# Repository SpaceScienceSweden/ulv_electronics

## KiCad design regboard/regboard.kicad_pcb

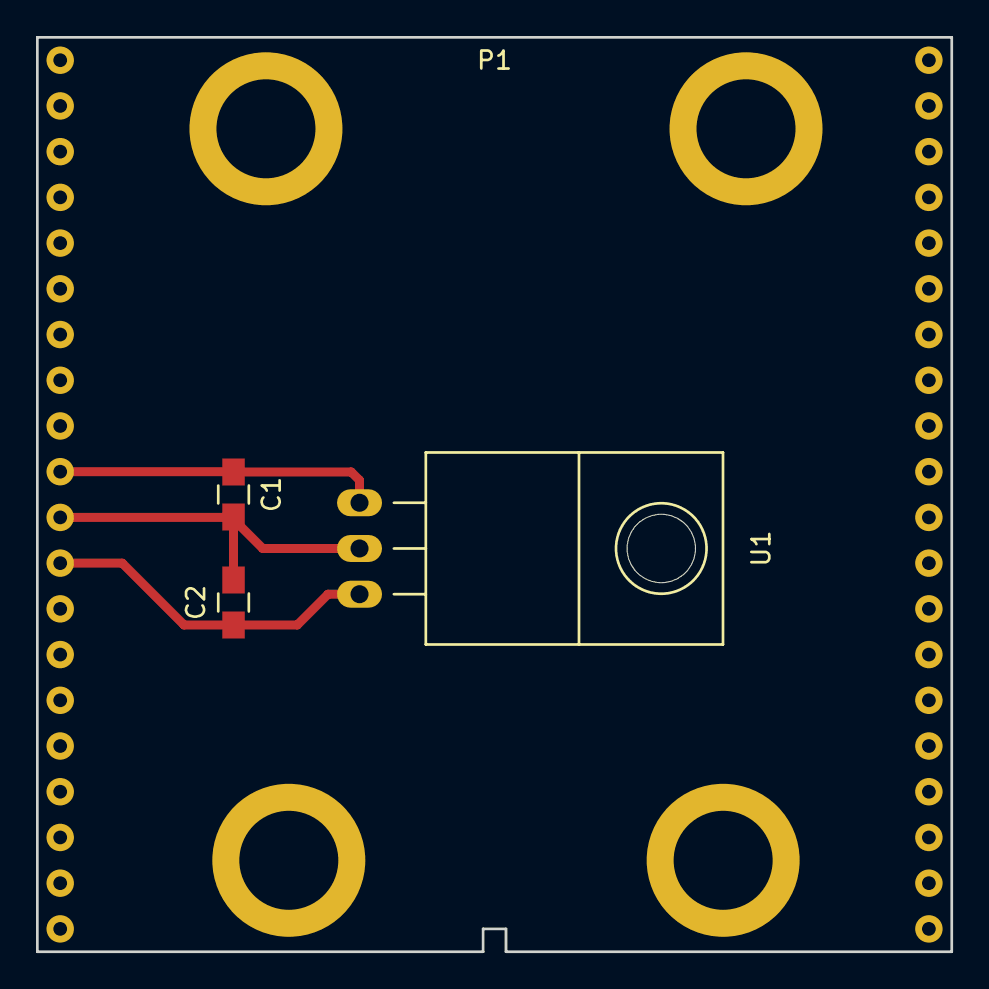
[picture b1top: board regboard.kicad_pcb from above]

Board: 2 copper layers, 50.8 x 50.8 mm, 4 parts (0 on the bottom side), 3 nets.

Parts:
C1: 10u; C_0805_HandSoldering
C2: 100n; C_0805_HandSoldering
P1: SCUBE40; scube40
U1: LM7812ACT; TO-220_Neutral123_Horizontal

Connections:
unnamed: C1.1, P1.10, U1.1
unnamed: C1.2, C2.2, P1.11, U1.2
unnamed: C2.1, P1.12, U1.3

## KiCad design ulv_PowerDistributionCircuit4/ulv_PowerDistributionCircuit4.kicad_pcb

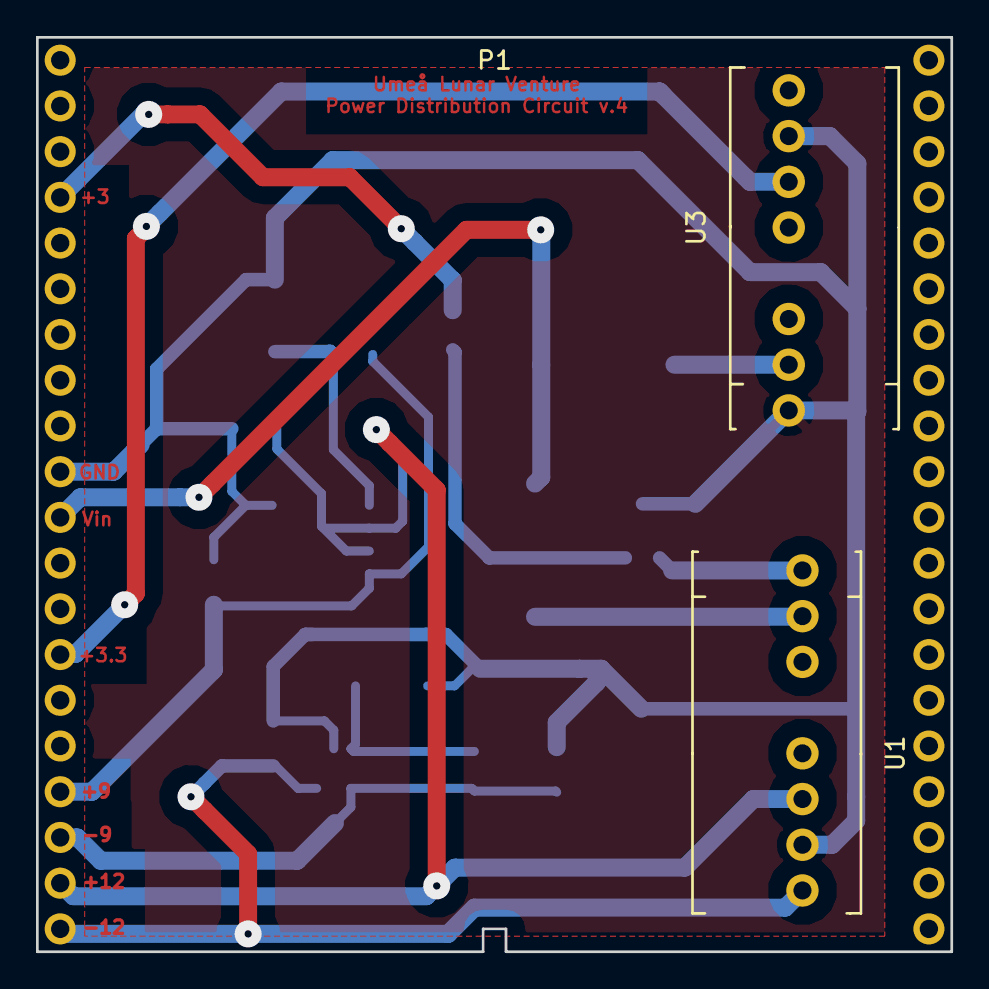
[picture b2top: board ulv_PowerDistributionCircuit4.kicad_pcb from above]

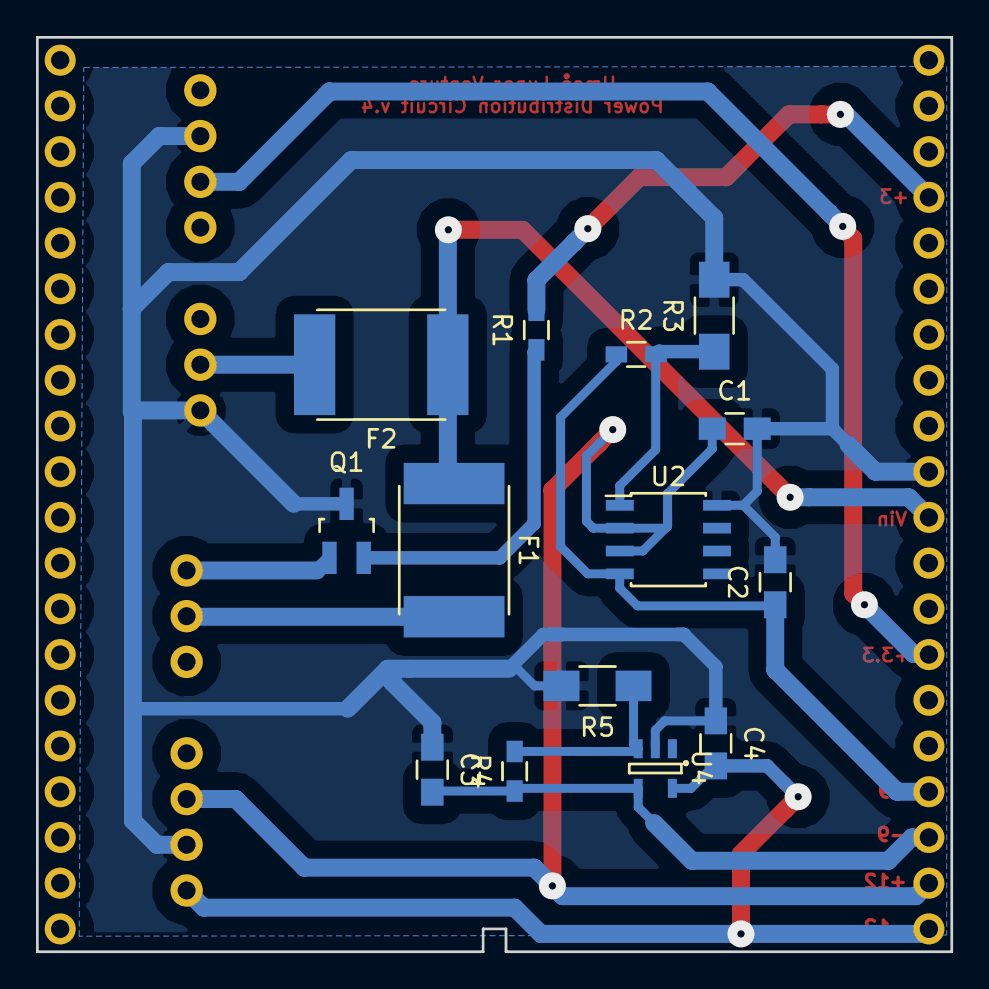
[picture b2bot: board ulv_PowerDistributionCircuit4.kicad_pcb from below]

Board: 2 copper layers, 50.8 x 50.8 mm, 17 parts (14 on the bottom side), 14 nets.

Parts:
C1: 0.1uF; C_0805_HandSoldering
C2, C3, C4: 10uF; C_0805_HandSoldering
F1, F2: F_Small; Fuse_SMD2920
P1: SCUBE40; scube40_no_holes
Q1: Q_NJFET_DGS; SOT-23_Handsoldering
R1: 10kO; R_0603_HandSoldering
R2, R4: 140kO; R_0603_HandSoldering
R3: 21.7kO; R_1206_HandSoldering
R5: 21.5kO; R_1206_HandSoldering
U1: RSO-2412D-Dual +/- 12V; RSO-2412D
U2: MAX1659 +9V; SOIC-8_3.9x4.9mm_Pitch1.27mm
U3: RSO-2412D-Single +3.3V; RSO-2412D
U4: MIC5270YM5-TR -9V; SOT-23-5

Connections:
unnamed: C1.1, P1.19, U1.6, U2.2, U2.3
unnamed: C1.2, C2.2, C3.1, C4.1, P1.10, Q1.3, R3.2, R5.2, U1.7, U2.8, U3.1, U3.7, U4.2
unnamed: C2.1, P1.17, R2.1, U2.4
unnamed: C3.2, P1.18, R4.1, U4.4
unnamed: C4.2, P1.20, U1.8, U4.5
unnamed: F1.1, F2.1, P1.11
unnamed: F1.2, U1.2
unnamed: F2.2, U3.2
unnamed: P1.4, R1.2
unnamed: P1.14, U3.6
unnamed: Q1.1, U1.1
unnamed: Q1.2, R1.1
unnamed: R2.2, R3.1, U2.1
unnamed: R4.2, R5.1, U4.3

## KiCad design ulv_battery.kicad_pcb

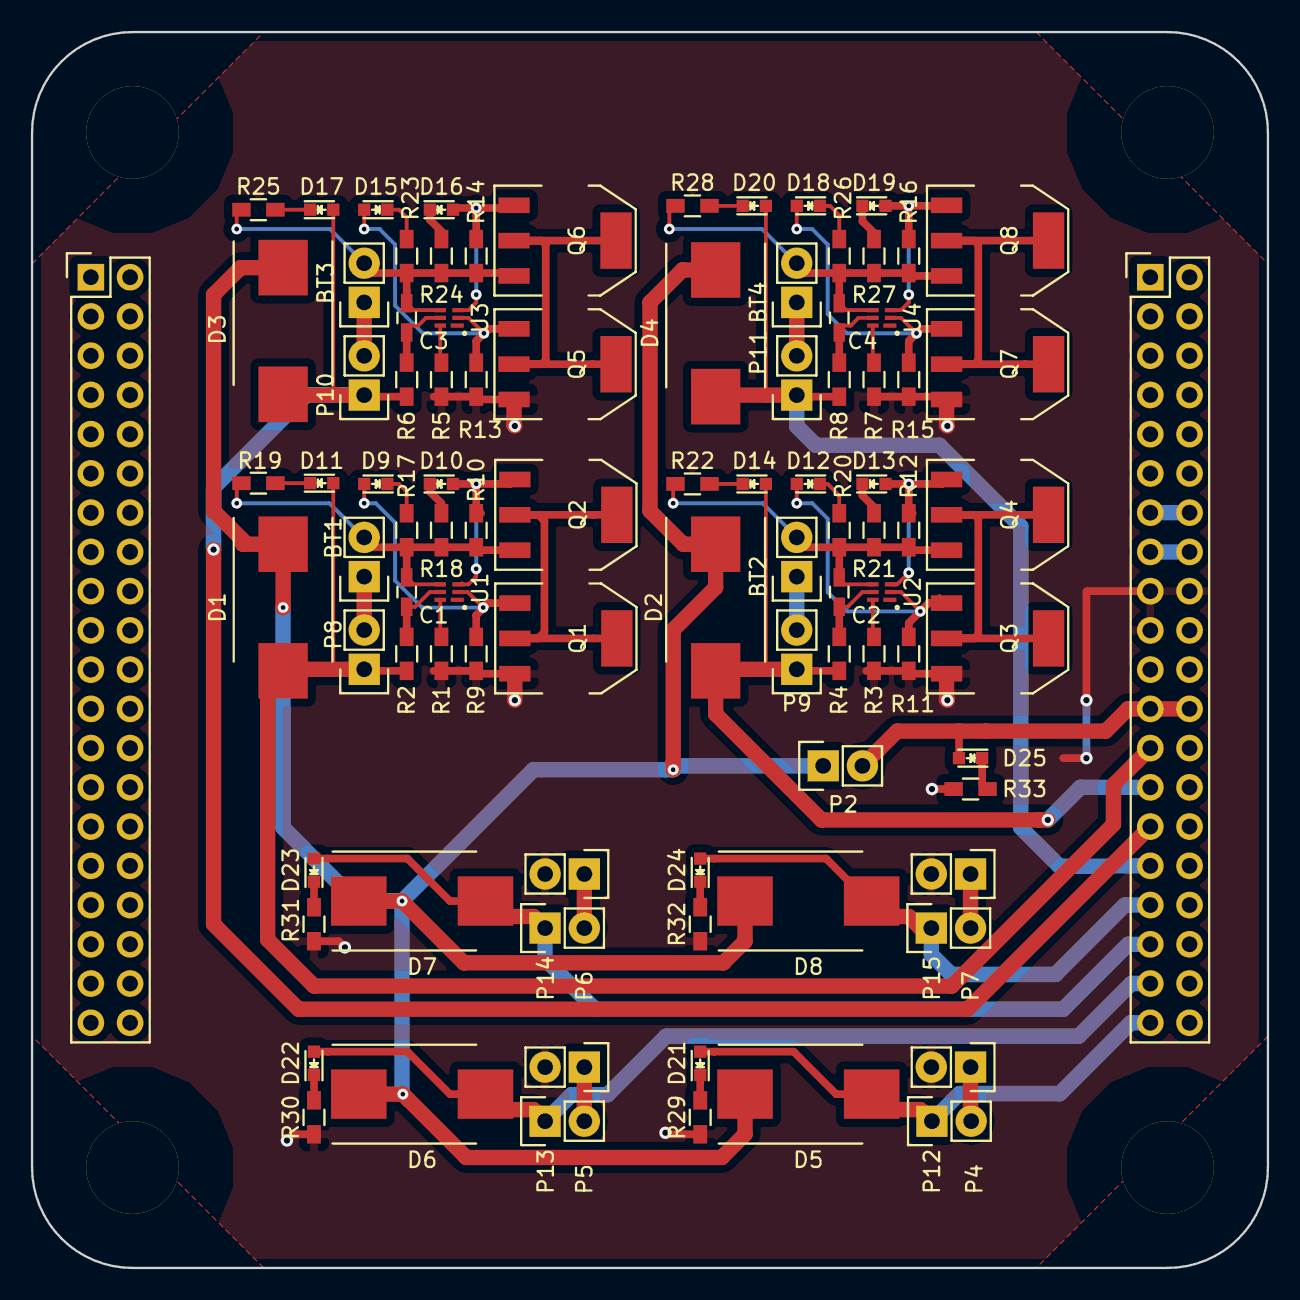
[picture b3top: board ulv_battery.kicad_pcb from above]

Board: 4 copper layers, 80.0 x 80.0 mm, 92 parts (0 on the bottom side), 62 nets.

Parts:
BT1, BT2, BT3, BT4: Battery; Pin_Header_Straight_1x02
C1, C2, C3, C4: 100n; C_0603_HandSoldering
D1, D2, D3, D4, D5, D6, D7, D8: Schottky; DO-214AB_Handsoldering
D9, D12, D15, D18, D25: GREEN; LED_0603
D10, D13, D16, D19: RED; LED_0603
D11, D14, D17, D20, D21, D22, D23, D24: ORANGE; LED_0603
P1: SCUBE80; scube80
P2, P8, P9, P10, P11, P12, P13, P14, P15: CONN_01X02; Pin_Header_Straight_1x02
P4, P5, P6, P7: PHOTOVOLTAIC; Pin_Header_Straight_1x02
Q1, Q2, Q3, Q4, Q5, Q6, Q7, Q8: Q_NMOS_GDSD; SOT-223
R1, R3, R5, R7, R17, R18, R19, R20, R21, R22, R23, R24, R25, R26, R27, R28, R29, R30, R31, R32, R33: 2k2; R_0603_HandSoldering
R2, R4, R6, R8: 330; R_0603_HandSoldering
R9, R10, R11, R12, R13, R14, R15, R16: 4M7; R_0603_HandSoldering
U1, U2, U3, U4: bq2970

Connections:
+3V3: P1.15A, P1.16A
+5V: P1.13A, P1.14A
/Battery 1/VBAT: D1.2, D11.2, P1.25A, P8.1, R2.1
/Battery 1/VSYS: D1.1, D2.1, D3.1, D4.1, D5.1, D6.1, D7.1, D8.1, P2.1
/Battery 2/VBAT: D2.2, D14.2, P1.27A, P9.1, R4.1
/Battery 3/VBAT: D3.2, D17.2, P1.29A, P10.1, R6.1
/Battery 4/VBAT: D4.2, D20.2, P1.31A, P11.1, R8.1
/Solar 1/VPV: D5.2, D21.2, P1.39A, P12.1
/Solar 2/VPV: D6.2, D22.2, P1.37A, P13.1
/Solar 3/VPV: D7.2, D23.2, P1.35A, P14.1
/Solar 4/VPV: D8.2, D24.2, P1.33A, P15.1
/VSYS: D25.2, P1.23A, P1.24A, P2.2
GND: P1.17A, P1.18A, P1.19A, P4.2, P5.2, P6.2, P7.2, Q1.3, Q3.3, Q5.3, Q7.3, R1.2, R3.2, R5.2, R7.2, R9.2, R11.2, R13.2, R15.2, R29.2, R30.2, R31.2, R32.2, R33.2
unnamed: BT1.1, P8.2
unnamed: BT1.2, C1.2, Q2.3, R10.2, R17.2, R18.2, R19.2, U1.4
unnamed: BT2.1, P9.2
unnamed: BT2.2, C2.2, Q4.3, R12.2, R20.2, R21.2, R22.2, U2.4
unnamed: BT3.1, P10.2
unnamed: BT3.2, C3.2, Q6.3, R14.2, R23.2, R24.2, R25.2, U3.4
unnamed: BT4.1, P11.2
unnamed: BT4.2, C4.2, Q8.3, R16.2, R26.2, R27.2, R28.2, U4.4
unnamed: C1.1, R2.2, U1.5
unnamed: C2.1, R4.2, U2.5
unnamed: C3.1, R6.2, U3.5
unnamed: C4.1, R8.2, U4.5
unnamed: D9.1, R17.1
unnamed: D9.2, Q1.1, R9.1, U1.2
unnamed: D10.1, R18.1
unnamed: D10.2, Q2.1, R10.1, U1.3
unnamed: D11.1, R19.1
unnamed: D12.1, R20.1
unnamed: D12.2, Q3.1, R11.1, U2.2
unnamed: D13.1, R21.1
unnamed: D13.2, Q4.1, R12.1, U2.3
unnamed: D14.1, R22.1
unnamed: D15.1, R23.1
unnamed: D15.2, Q5.1, R13.1, U3.2
unnamed: D16.1, R24.1
unnamed: D16.2, Q6.1, R14.1, U3.3
unnamed: D17.1, R25.1
unnamed: D18.1, R26.1
unnamed: D18.2, Q7.1, R15.1, U4.2
unnamed: D19.1, R27.1
unnamed: D19.2, Q8.1, R16.1, U4.3
unnamed: D20.1, R28.1
unnamed: D21.1, R29.1
unnamed: D22.1, R30.1
unnamed: D23.1, R31.1
unnamed: D24.1, R32.1
unnamed: D25.1, R33.1
unnamed: P4.1, P12.2
unnamed: P5.1, P13.2
unnamed: P6.1, P14.2
unnamed: P7.1, P15.2
unnamed: Q1.2, Q1.4, Q2.2, Q2.4
unnamed: Q3.2, Q3.4, Q4.2, Q4.4
unnamed: Q5.2, Q5.4, Q6.2, Q6.4
unnamed: Q7.2, Q7.4, Q8.2, Q8.4
unnamed: R1.1, U1.6
unnamed: R3.1, U2.6
unnamed: R5.1, U3.6
unnamed: R7.1, U4.6

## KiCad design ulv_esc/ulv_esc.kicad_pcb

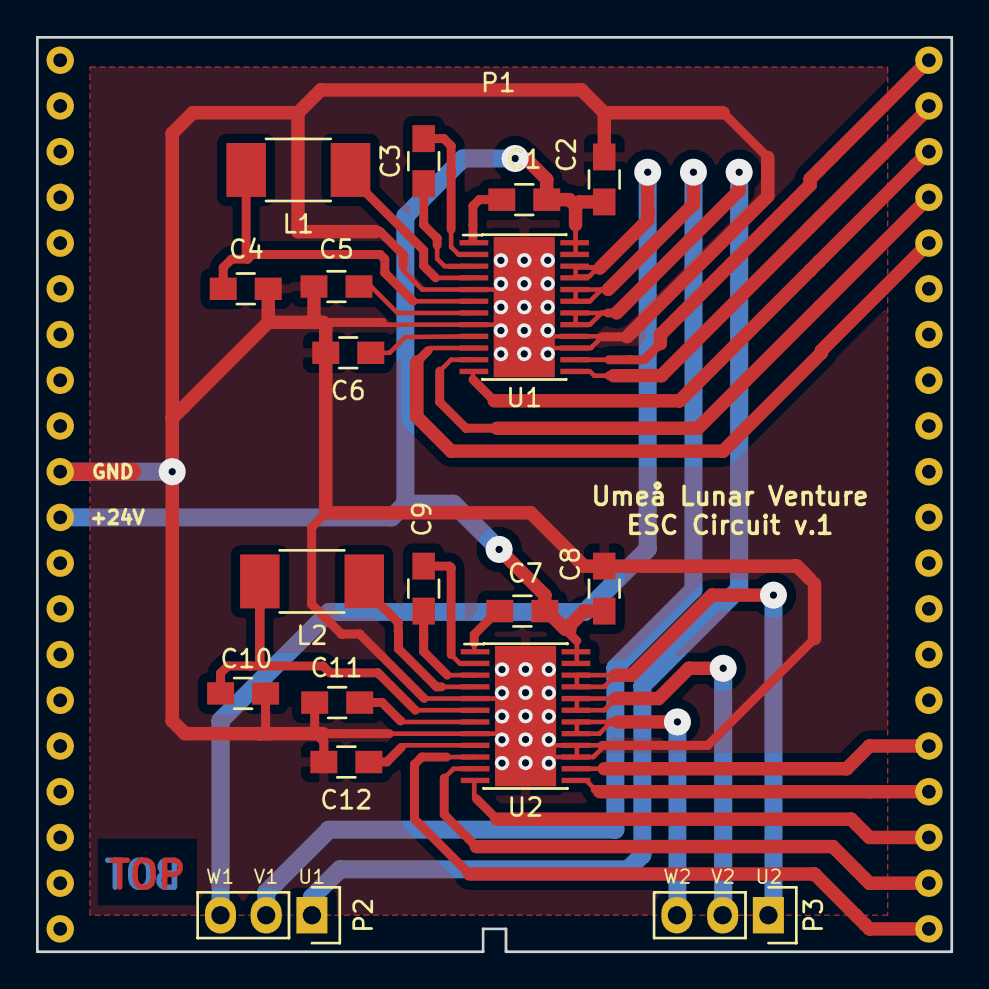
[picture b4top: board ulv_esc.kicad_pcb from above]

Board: 2 copper layers, 50.8 x 50.8 mm, 19 parts (0 on the bottom side), 32 nets.

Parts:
C1, C3, C7, C9: 0.1 uF; C_0805_HandSoldering
C2, C4, C8, C10: 10 uF; C_0805_HandSoldering
C5, C6, C11, C12: 1 uF; C_0805_HandSoldering
L1, L2: 47 uH; C_1812_HandSoldering
P1: SCUBE40; scube40_no_holes
P2, P3: CONN_01X03; Pin_Header_Straight_1x03
U1, U2: DRV10983; TSSOP-24_Pitch0.65mm_PowerPad

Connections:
GND: C2.2, C4.1, C5.2, C6.2, C8.2, C10.1, C11.2, C12.2, P1.10, U1.5, U1.8, U1.15, U1.16, U1.25, U2.5, U2.8, U2.15, U2.16, U2.25
unnamed: C1.1, C2.1, C7.1, C8.1, P1.11, U1.23, U1.24, U2.23, U2.24
unnamed: C1.2, U1.1
unnamed: C3.1, U1.3
unnamed: C3.2, U1.2
unnamed: C4.2, L1.2, U1.6
unnamed: C5.1, U1.7
unnamed: C6.1, U1.9
unnamed: C7.2, U2.1
unnamed: C9.1, U2.3
unnamed: C9.2, U2.2
unnamed: C10.2, L2.2, U2.6
unnamed: C11.1, U2.7
unnamed: C12.1, U2.9
unnamed: L1.1, U1.4
unnamed: L2.1, U2.4
unnamed: P1.21, U2.10
unnamed: P1.22, U2.11
unnamed: P1.23, U2.12
unnamed: P1.24, U2.13
unnamed: P1.25, U2.14
unnamed: P1.36, U1.10
unnamed: P1.37, U1.11
unnamed: P1.38, U1.12
unnamed: P1.39, U1.13
unnamed: P1.40, U1.14
unnamed: P2.1, U1.17, U1.18
unnamed: P2.2, U1.19, U1.20
unnamed: P2.3, U1.21, U1.22
unnamed: P3.1, U2.21, U2.22
unnamed: P3.2, U2.19, U2.20
unnamed: P3.3, U2.17, U2.18

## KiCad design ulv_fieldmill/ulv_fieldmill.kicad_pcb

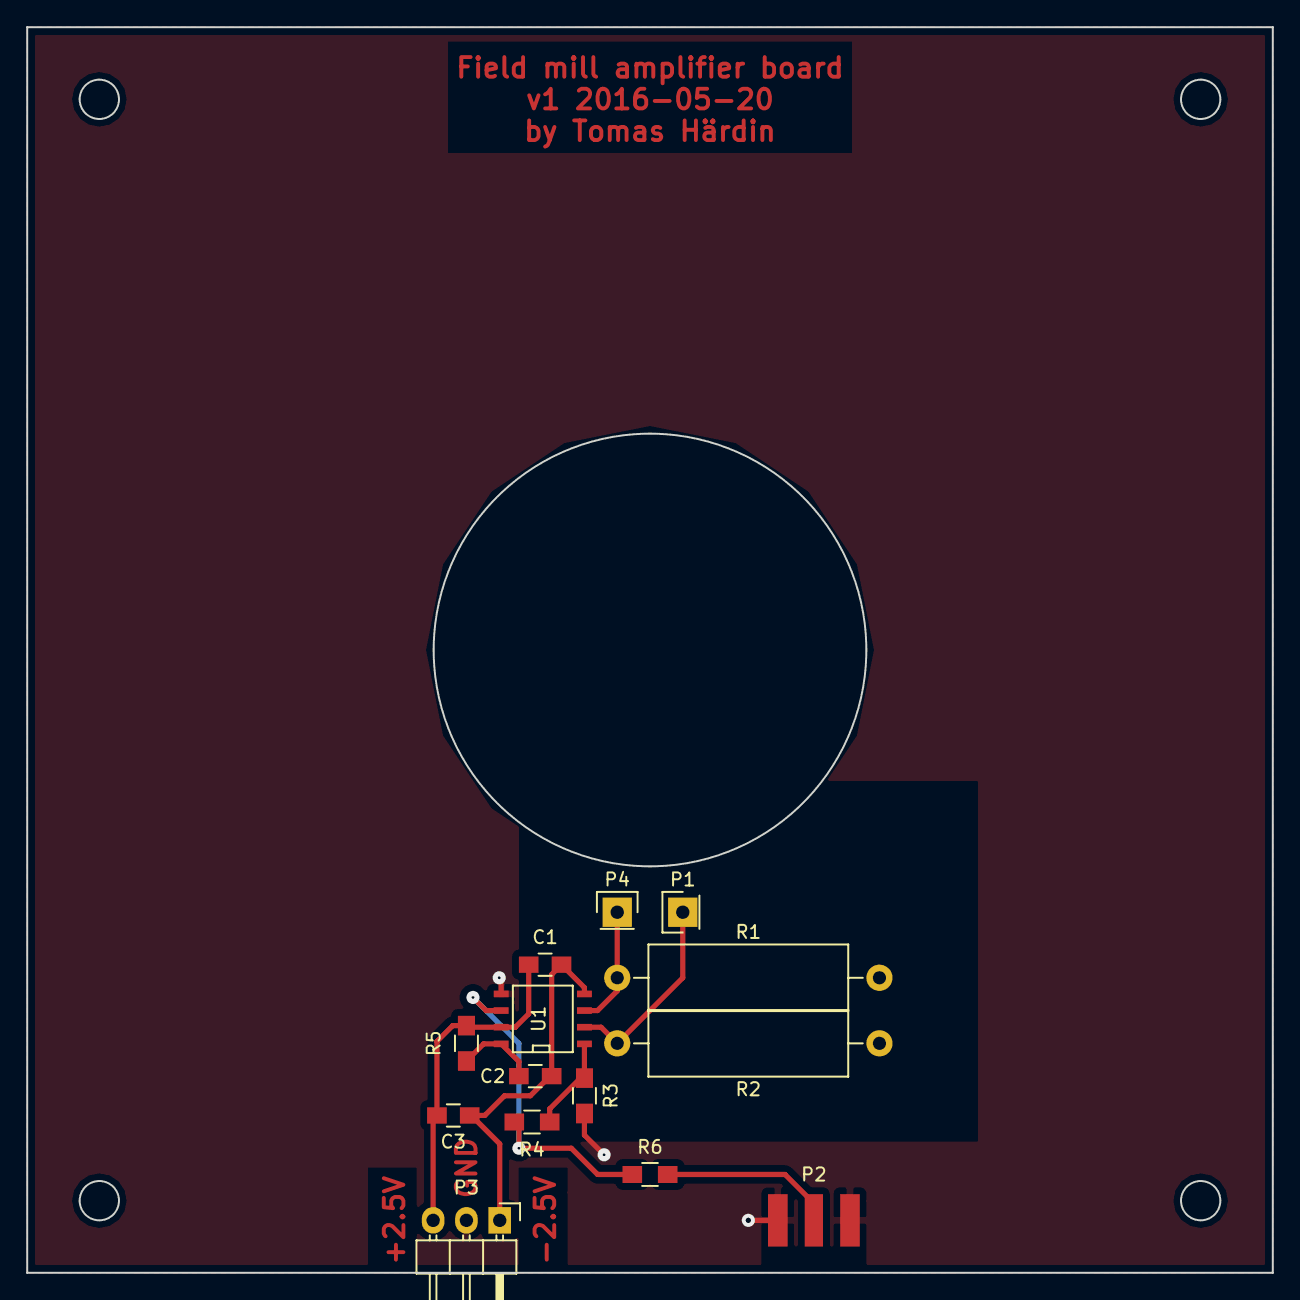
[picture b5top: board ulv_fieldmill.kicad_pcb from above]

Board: 2 copper layers, 95.0 x 95.0 mm, 14 parts (0 on the bottom side), 9 nets.

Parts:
C1, C2: 100n; C_0805_HandSoldering
C3: 1u; C_0805_HandSoldering
P1, P4: CONN_01X01; Pin_Header_Straight_1x01
P2: SMA; SMA-edge
P3: CONN_01X03; Pin_Header_Angled_1x03
R1, R2: 1M; Resistor_Horizontal_RM20mm
R3, R6: 1k; R_0805_HandSoldering
R4, R5: 100k; R_0805_HandSoldering
U1: MCP6N11; SOIC-8-N

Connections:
GND: P2.2, P3.2, R1.1, R2.1, R3.1, U1.5
unnamed: C2.1, R5.2, U1.8
unnamed: P1.1, R2.2, U1.2
unnamed: P2.1, R6.2
unnamed: P4.1, R1.2, U1.3
unnamed: R3.2, R4.1, U1.1
unnamed: R4.2, R6.1, U1.6
VDD: C1.1, C3.1, P3.3, R5.1, U1.7
VSS: C1.2, C2.2, C3.2, P3.1, U1.4

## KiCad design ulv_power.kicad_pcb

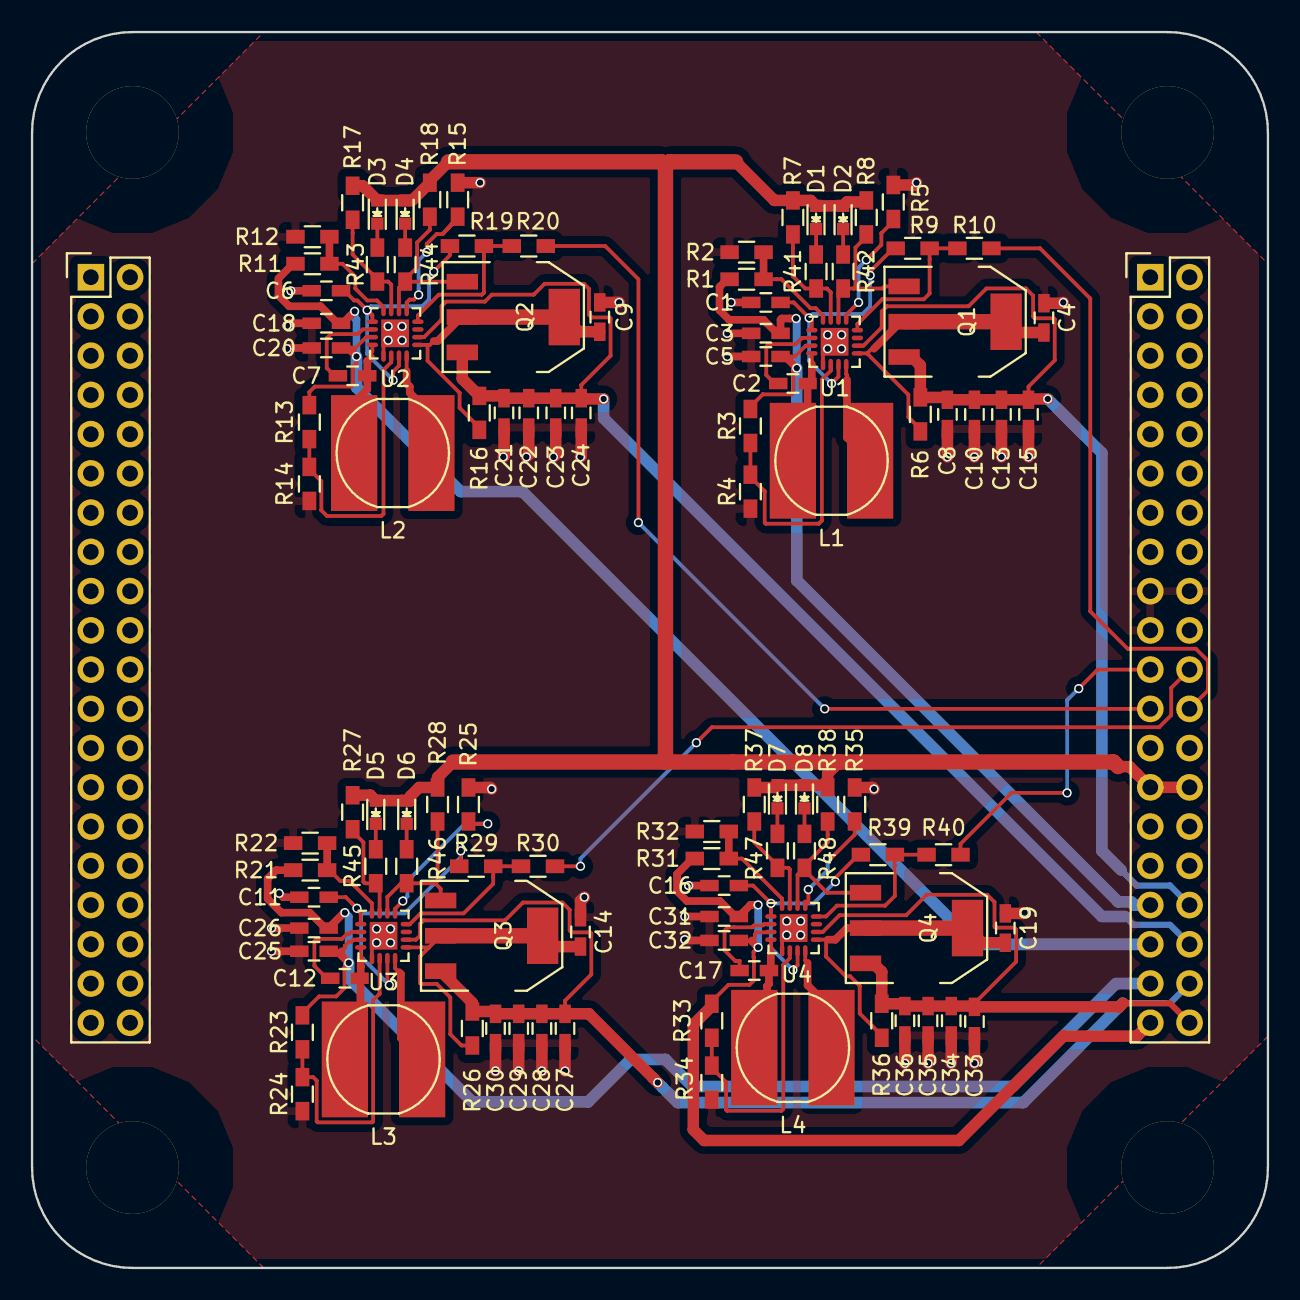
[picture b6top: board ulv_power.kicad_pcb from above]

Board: 4 copper layers, 80.0 x 80.0 mm, 105 parts (0 on the bottom side), 66 nets.

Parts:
C1, C6, C11, C16: 2.2uF; C_0603_HandSoldering
C2, C7, C12, C17: 22nF; C_0603_HandSoldering
C3, C4, C5, C8, C9, C10, C13, C14, C15, C18, C19, C20, C21, C22, C23, C24, C25, C26, C27, C28, C29, C30, C31, C32, C33, C34, C35, C36: 4.7uF; C_0603_HandSoldering
D1, D3, D5, D7: RED; LED_0603
D2, D4, D6, D8: GREEN; LED_0603
L1, L2, L3, L4: 12uH; SDE0805A
P1: SCUBE80; scube80
Q1, Q2, Q3, Q4: FDT434P; SOT-223
R1, R2, R7, R8, R11, R12, R17, R18, R21, R22, R27, R28, R31, R32, R37, R38: 47k; R_0603_HandSoldering
R3, R13, R23, R33: 10.0k; R_0603_HandSoldering
R4, R14, R24, R34: 1.67k; R_0603_HandSoldering
R5, R15, R25, R35: 3.01k; R_0603_HandSoldering
R6, R16, R26, R36: 470k; R_0603_HandSoldering
R9, R19, R29, R39: 8k2; R_0603_HandSoldering
R10, R20, R30, R40: 619; R_0603_HandSoldering
R41, R42, R43, R44, R45, R46, R47, R48: 2k2; R_0603_HandSoldering
U1, U2, U3, U4: LTC4121-4.2; QFN-16-1EP_3x3mm_Pitch0.5mm

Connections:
/chargerchannel1//CHRG: Q4.1, R38.1, R48.1, U4.14
/chargerchannel1//FAULT: R37.2, R47.1, U4.15
/chargerchannel1/NTC: P1.21A, R40.1
/chargerchannel1/PV_IN: C31.1, C32.1, P1.39A, R31.2, R33.2, U4.3
/chargerchannel1/RUN: R31.1, R32.1, U4.16
/chargerchannel1/VBAT: C33.1, C34.1, C35.1, C36.1, P1.40A, Q4.3, R36.1, U4.10
/chargerchannel1/VSYS: D1.2, D2.2, D3.2, D4.2, D5.2, D6.2, D7.2, D8.2, P1.27A, P1.28A, R7.1, R8.2, R17.1, R18.2, R27.1, R28.2, R37.1, R38.2
/chargerchannel2//CHRG: Q3.1, R28.1, R46.1, U3.14
/chargerchannel2//FAULT: R27.2, R45.1, U3.15
/chargerchannel2/NTC: P1.22A, R30.1
/chargerchannel2/PV_IN: C25.1, C26.1, P1.37A, R21.2, R23.2, U3.3
/chargerchannel2/RUN: R21.1, R22.1, U3.16
/chargerchannel2/VBAT: C27.1, C28.1, C29.1, C30.1, P1.38A, Q3.3, R26.1, U3.10
/chargerchannel3//CHRG: Q2.1, R18.1, R44.1, U2.14
/chargerchannel3//FAULT: R17.2, R43.1, U2.15
/chargerchannel3/NTC: P1.23A, R20.1
/chargerchannel3/PV_IN: C18.1, C20.1, P1.35A, R11.2, R13.2, U2.3
/chargerchannel3/RUN: R11.1, R12.1, U2.16
/chargerchannel3/VBAT: C21.1, C22.1, C23.1, C24.1, P1.36A, Q2.3, R16.1, U2.10
/chargerchannel4//CHRG: Q1.1, R8.1, R42.1, U1.14
/chargerchannel4//FAULT: R7.2, R41.1, U1.15
/chargerchannel4/NTC: P1.24A, R10.1
/chargerchannel4/PV_IN: C3.1, C5.1, P1.33A, R1.2, R3.2, U1.3
/chargerchannel4/RUN: R1.1, R2.1, U1.16
/chargerchannel4/VBAT: C8.1, C10.1, C13.1, C15.1, P1.34A, Q1.3, R6.1, U1.10
GND: C1.1, C3.2, C4.2, C5.2, C6.1, C8.2, C9.2, C10.2, C11.1, C13.2, C14.2, C15.2, C16.1, C18.2, C19.2, C20.2, C21.2, C22.2, C23.2, C24.2, C25.2, C26.2, C27.2, C28.2, C29.2, C30.2, C31.2, C32.2, C33.2, C34.2, C35.2, C36.2, P1.17A, P1.18A, P1.19A, R2.2, R4.2, R5.1, R12.2, R14.2, R15.1, R22.2, R24.2, R25.1, R32.2, R34.2, R35.1, U1.5, U1.17, U2.5, U2.17, U3.5, U3.17, U4.5, U4.17
unnamed: C1.2, R9.2, U1.1, U1.7
unnamed: C2.1, L1.1, U1.4
unnamed: C2.2, U1.2
unnamed: C4.1, Q1.2, Q1.4, R6.2, U1.9
unnamed: C6.2, R19.2, U2.1, U2.7
unnamed: C7.1, L2.1, U2.4
unnamed: C7.2, U2.2
unnamed: C9.1, Q2.2, Q2.4, R16.2, U2.9
unnamed: C11.2, R29.2, U3.1, U3.7
unnamed: C12.1, L3.1, U3.4
unnamed: C12.2, U3.2
unnamed: C14.1, Q3.2, Q3.4, R26.2, U3.9
unnamed: C16.2, R39.2, U4.1, U4.7
unnamed: C17.1, L4.1, U4.4
unnamed: C17.2, U4.2
unnamed: C19.1, Q4.2, Q4.4, R36.2, U4.9
unnamed: D1.1, R41.2
unnamed: D2.1, R42.2
unnamed: D3.1, R43.2
unnamed: D4.1, R44.2
unnamed: D5.1, R45.2
unnamed: D6.1, R46.2
unnamed: D7.1, R47.2
unnamed: D8.1, R48.2
unnamed: L1.2, U1.8
unnamed: L2.2, U2.8
unnamed: L3.2, U3.8
unnamed: L4.2, U4.8
unnamed: R3.1, R4.1, U1.6
unnamed: R5.2, U1.13
unnamed: R9.1, R10.2, U1.12
unnamed: R13.1, R14.1, U2.6
unnamed: R15.2, U2.13
unnamed: R19.1, R20.2, U2.12
unnamed: R23.1, R24.1, U3.6
unnamed: R25.2, U3.13
unnamed: R29.1, R30.2, U3.12
unnamed: R33.1, R34.1, U4.6
unnamed: R35.2, U4.13
unnamed: R39.1, R40.2, U4.12

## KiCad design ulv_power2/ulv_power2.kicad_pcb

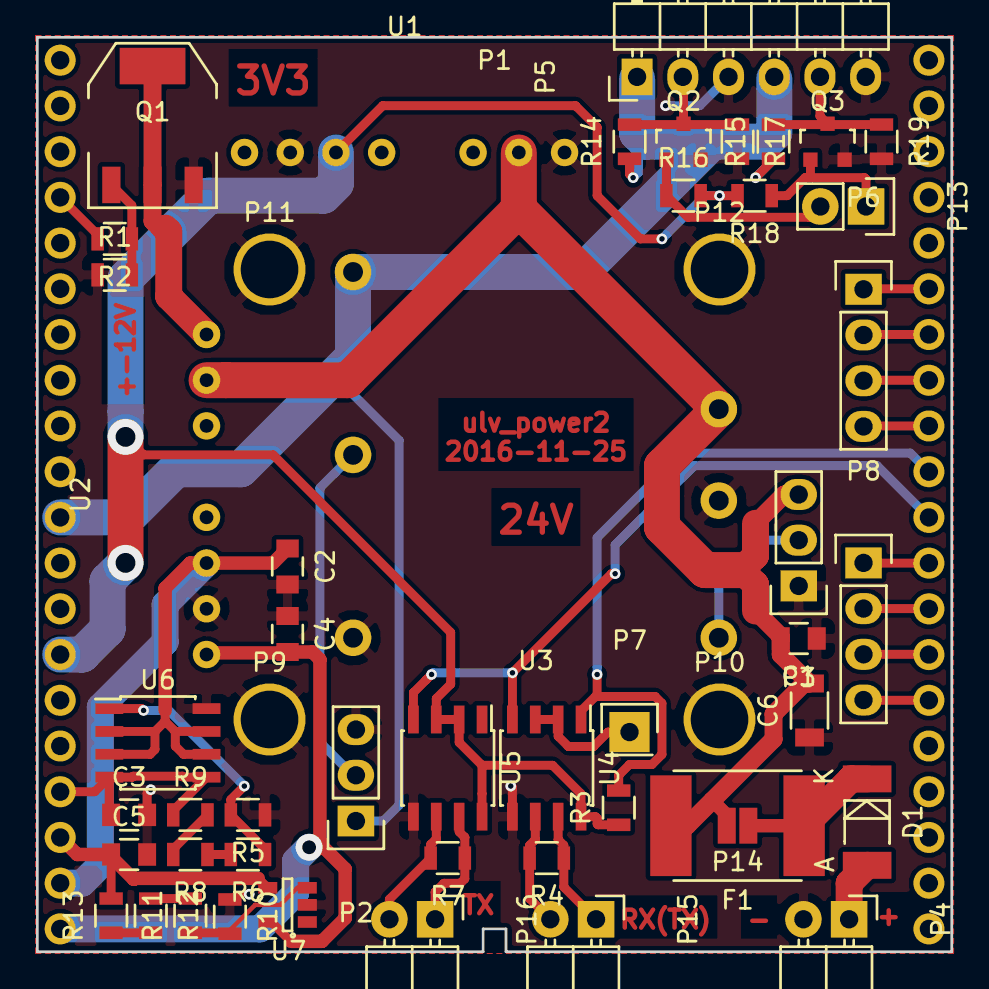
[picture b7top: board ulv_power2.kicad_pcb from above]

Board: 2 copper layers, 50.8 x 50.8 mm, 53 parts (0 on the bottom side), 40 nets.

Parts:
C1, C3, C5: 10u; C_0805
C2, C4: 100n; C_0805
C6: 100u; C_1206
D1: SMS240; MELF_Standard
F1: PTC; Fuse_SMD2920
P1: SCUBE40; scube40_no_holes
P2: TRIM; Pin_Header_Straight_1x03
P3: ON/OFF; Pin_Header_Straight_1x03
P4: PWR; Pin_Header_Angled_1x02
P5: MOTOR_OUT; Pin_Header_Angled_1x06
P6: DE2; Pin_Header_Straight_1x04
P7: DE; Pin_Header_Straight_1x01
P8: DE1; Pin_Header_Straight_1x04
P9, P10, P11, P12: M3; M3_PTH
P13: PWM; Pin_Header_Straight_1x02
P14: FUSE_BYPASS; solder_bridge
P15: IN; Pin_Header_Angled_1x02
P16: OUT; Pin_Header_Angled_1x02
Q1: IRLL024NPBF; SOT-223
Q2, Q3: PMBF170; SOT-23
R1: 1M; R_0805
R2, R3, R5, R10: 10k; R_0805
R4, R7: 120; R_0805
R6, R11: 56k; R_0805
R8, R12: 8k2; R_0805
R9: 180; R_0805
R13: 820; R_0805
R14, R15, R16, R17, R18, R19: 100k; R_0805
U1: RS-243.3S; RSO-2412D_v2
U2: RSO-2412D-Dual; RSO-2412D_v2
U3: THN_30-2415
U4, U5: MAX485; SOIC-8_3.9x4.9mm_Pitch1.27mm
U6: MAX1659; SOIC-8_3.9x4.9mm_Pitch1.27mm
U7: MIC5270YM5-TR; SOT-23-5

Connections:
+3V3: P1.14, R3.1, R16.2, R18.2, U1.6, U4.8, U5.2, U5.3, U5.8
+9V: C3.1, P1.17, R9.1, U6.4, U6.5
+12V: C2.1, P1.19, U2.6, U6.2, U6.3, U6.6, U6.7
+24V: P1.11, P2.1, P5.1, P5.4, R14.1, R15.1, U3.3
-9VA: C5.1, P1.18, R13.2, U7.4
-12VA: C4.2, P1.20, U2.8, U7.5
/A: P15.2, R4.2, U4.6
/B: P15.1, R4.1, U4.7
/EN_APWR: P1.4, R2.2
/RX: P1.31, R3.2, U4.1
/TX: P1.30, U4.4, U5.4
/Y: P16.2, R7.2, U5.6
/Z: P16.1, R7.1, U5.7
GND: C1.1, C2.2, C3.2, C4.1, C5.2, C6.1, P1.10, P2.3, P3.1, P4.2, P5.3, P5.6, P9.1, P10.1, P11.1, P12.1, Q1.3, Q2.2, Q3.2, R1.1, R5.1, R10.1, R17.2, R19.2, U1.1, U1.7, U2.7, U3.2, U3.5, U4.5, U5.5, U6.8, U7.2
unnamed: D1.1, F1.1, P14.1
unnamed: D1.2, P4.1
unnamed: P1.26, P8.4
unnamed: P1.27, P8.3
unnamed: P1.28, P8.2
unnamed: P1.29, P8.1
unnamed: P1.32, P6.4
unnamed: P1.33, P6.3
unnamed: P1.34, P6.2
unnamed: P1.35, P6.1
unnamed: P2.2, U3.4
unnamed: P3.2, U3.6
unnamed: P5.2, Q2.3, R14.2, R17.1
unnamed: P5.5, Q3.3, R15.2, R19.1
unnamed: P7.1, U4.2, U4.3
unnamed: P13.1, Q3.1, R18.1
unnamed: P13.2, Q2.1, R16.1
unnamed: Q1.1, R1.2, R2.1
unnamed: Q1.2, Q1.4, U2.1
unnamed: R5.2, R6.1, U6.1
unnamed: R6.2, R8.1
unnamed: R8.2, R9.2
unnamed: R10.2, R11.1, U7.3
unnamed: R11.2, R12.1
unnamed: R12.2, R13.1
VIN: C1.2, C6.2, F1.2, P3.3, P14.2, U1.2, U2.2, U3.1
